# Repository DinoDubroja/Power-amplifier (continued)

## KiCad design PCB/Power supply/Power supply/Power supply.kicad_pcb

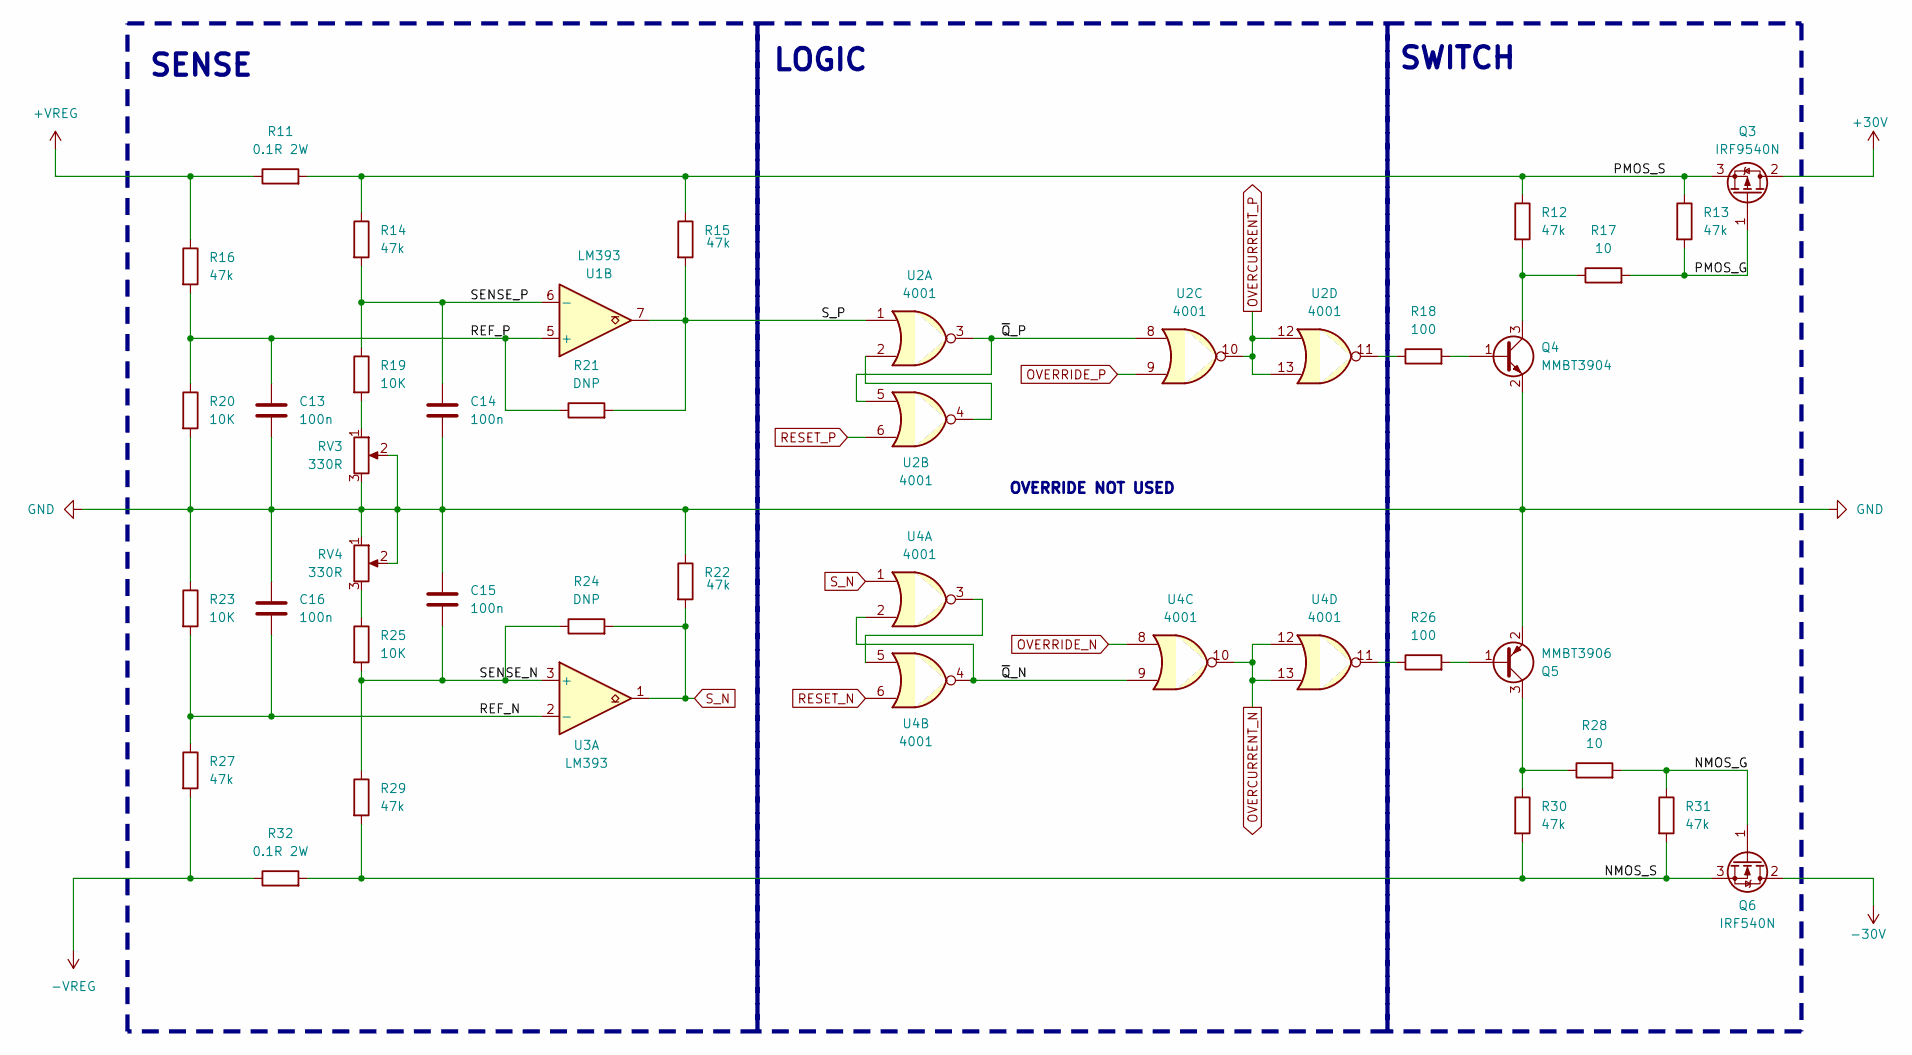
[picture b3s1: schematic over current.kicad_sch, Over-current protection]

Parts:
C13, C14, C15, C16: 100n; C_Rect_L7.0mm_W2.5mm_P5.00mm
Q3: IRF9540N; TO-220-3_Vertical
Q4: MMBT3904; SOT-23
Q5: MMBT3906; SOT-23
Q6: IRF540N; TO-220-3_Vertical
R11, R32: 0.1R 2W; R_Axial_DIN0309_L9.0mm_D3.2mm_P20.32mm_Horizontal
R12, R13, R14, R15, R16, R22, R27, R29, R30, R31: 47k; R_Axial_DIN0207_L6.3mm_D2.5mm_P10.16mm_Horizontal
R17, R28: 10; R_Axial_DIN0207_L6.3mm_D2.5mm_P10.16mm_Horizontal
R18, R26: 100; R_Axial_DIN0207_L6.3mm_D2.5mm_P10.16mm_Horizontal
R19, R20, R23, R25: 10K; R_Axial_DIN0207_L6.3mm_D2.5mm_P10.16mm_Horizontal
R21, R24: DNP; R_Axial_DIN0207_L6.3mm_D2.5mm_P10.16mm_Horizontal
RV3, RV4: 330R; Potentiometer_Bourns_3296W_Vertical
U1, U3: LM393; SOIC-8_3.9x4.9mm_P1.27mm
U2, U4: 4001; SOIC127P600X175-14N

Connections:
+30V: Q3.2 (D); also elsewhere on the board
+VREG: R11.1, R16.1; also elsewhere on the board
-30V: Q6.2 (D); also elsewhere on the board
-VREG: R27.2, R32.1; also elsewhere on the board
/Over-current/NMOS_G: Q6.1 (G), R28.2, R31.1
/Over-current/NMOS_S: Q6.3 (S), R29.2, R30.2, R31.2, R32.2
/Over-current/PMOS_G: Q3.1 (G), R13.2, R17.2
/Over-current/PMOS_S: Q3.3 (S), R11.2, R12.1, R13.1, R14.1, R15.1
/Over-current/REF_N: C16.2, R23.2, R27.1, U3.2 (-)
/Over-current/REF_P: C13.1, R16.2, R20.1, R21.1, U1.5 (+)
/Over-current/SENSE_N: C15.2, R24.1, R25.2, R29.1, U3.3 (+)
/Over-current/SENSE_P: C14.1, R14.2, R19.1, U1.6 (-)
/Over-current/S_P: R15.2, R21.2, U1.7, U2.1
/Over-current/~Q_N: U4.2, U4.4, U4.9
/Over-current/~Q_P: U2.3, U2.5, U2.8
GND: C13.2, C14.2, C15.1, C16.1, Q4.2 (E), Q5.2 (E), R20.2, R22.1, R23.1, RV3.2, RV3.3, RV4.1, RV4.2; also elsewhere on the board
unnamed: Q4.1 (B), R18.2
unnamed: Q4.3 (C), R12.2, R17.1
unnamed: Q5.1 (B), R26.2
unnamed: Q5.3 (C), R28.1, R30.1
unnamed: R18.1, U2.11
unnamed: R19.2, RV3.1
unnamed: R25.1, RV4.3
unnamed: R26.1, U4.11
unnamed: U2.2, U2.4
unnamed: U4.3, U4.5
OVERCURRENT_N: U4.10, U4.12, U4.13; also elsewhere on the board
OVERCURRENT_P: U2.10, U2.12, U2.13; also elsewhere on the board
OVERRIDE_N: U4.8; also elsewhere on the board
OVERRIDE_P: U2.9; also elsewhere on the board
RESET_N: U4.6; also elsewhere on the board
RESET_P: U2.6; also elsewhere on the board
S_N: R22.2, R24.2, U3.1, U4.1

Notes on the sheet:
SENSE
LOGIC
OVERRIDE NOT USED
SWITCH

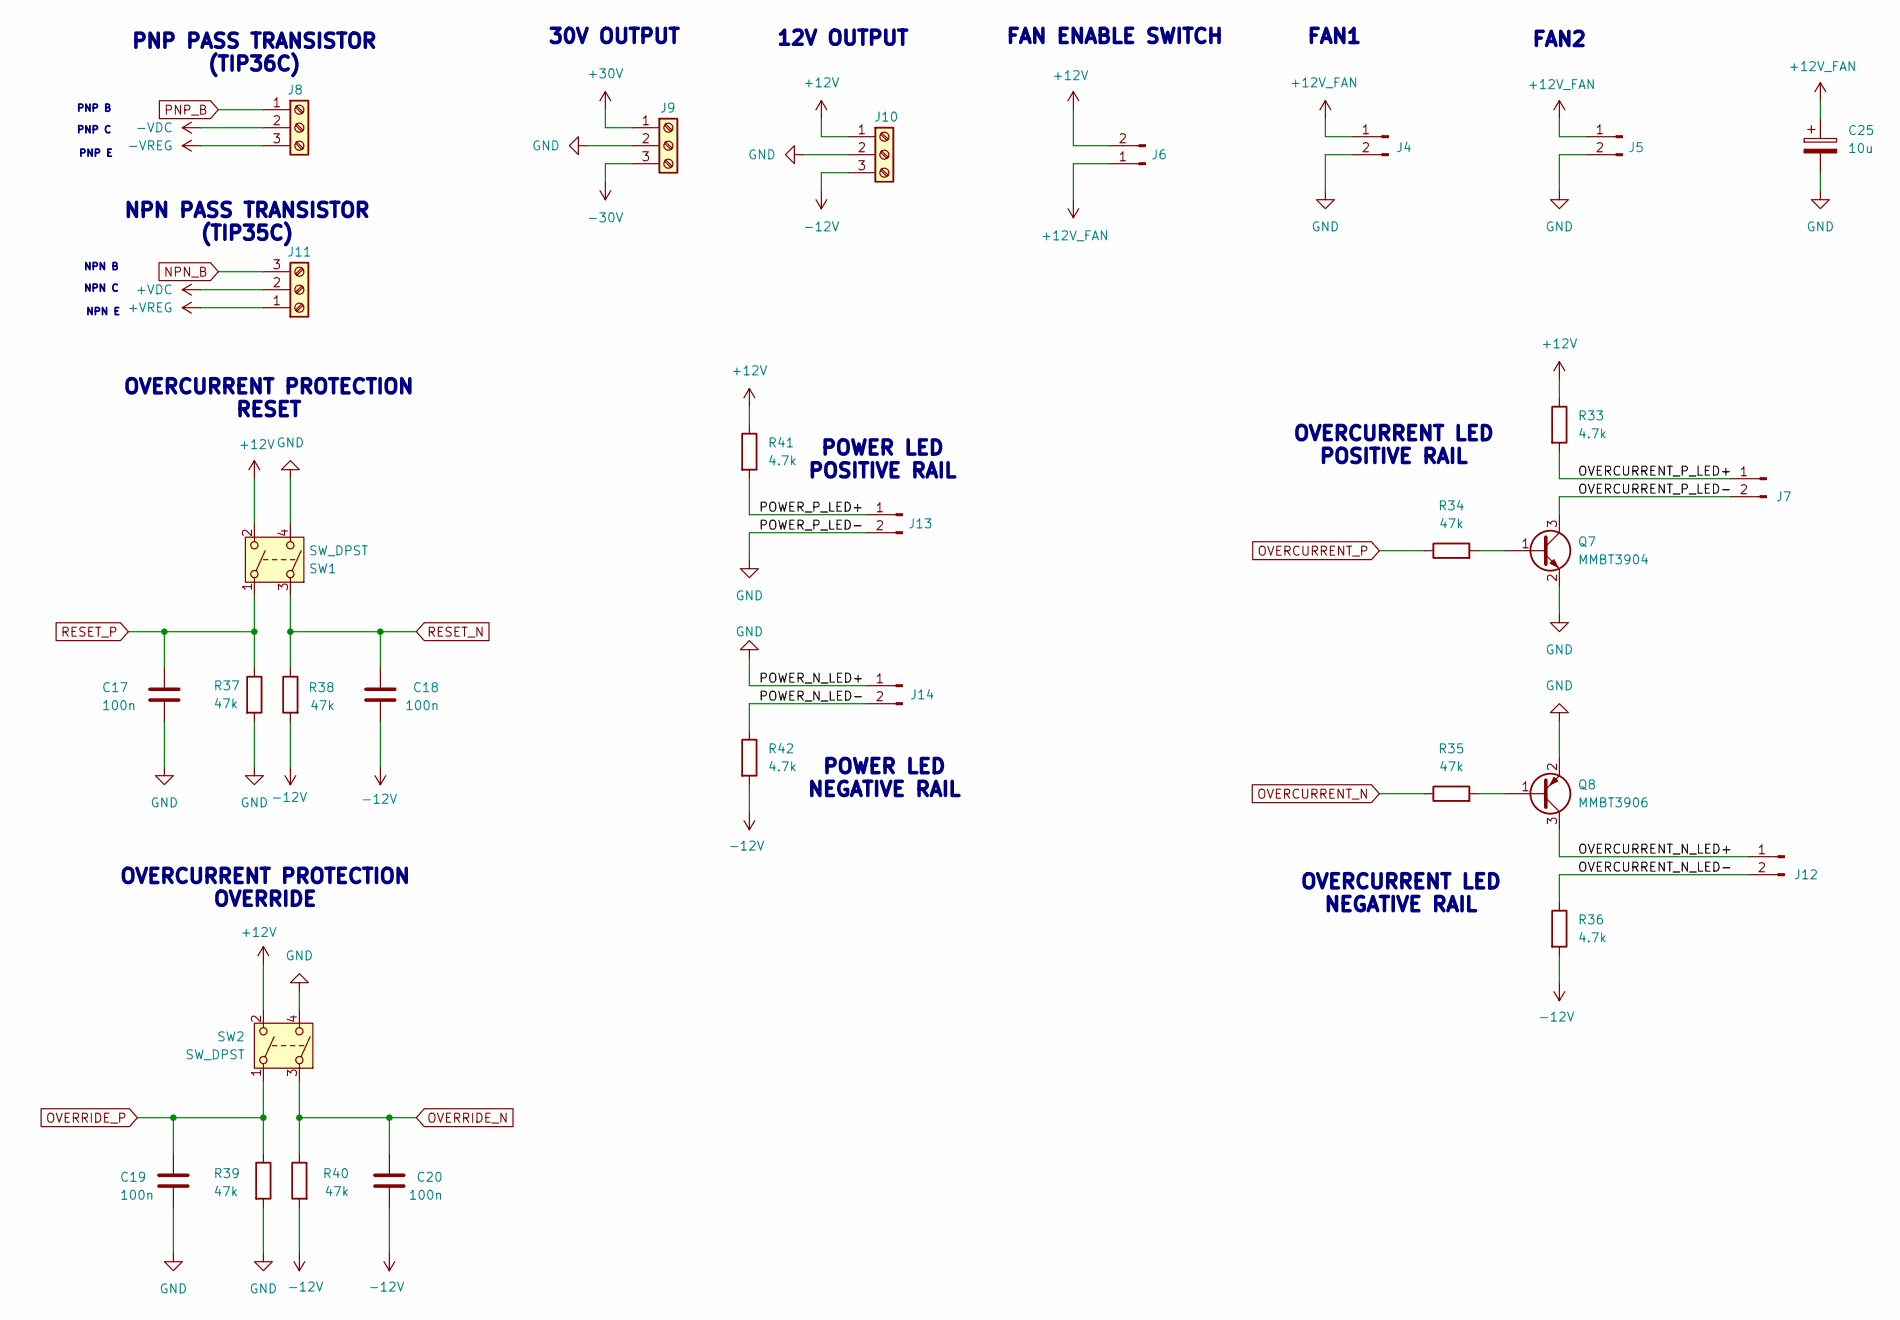
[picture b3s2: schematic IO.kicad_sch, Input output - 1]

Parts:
C17, C18, C19, C20: 100n; C_Rect_L7.0mm_W2.5mm_P5.00mm
C25: 10u; CP_Radial_D4.0mm_P2.00mm
J4, J5, J6, J7, J12, J13, J14: Conn_01x02_Pin; JST_XH_B2B-XH-A_1x02_P2.50mm_Vertical
J8, J9, J10, J11: Screw_Terminal_01x03; TerminalBlock_Phoenix_MKDS-1,5-3-5.08_1x03_P5.08mm_Horizont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
Q7: MMBT3904; SOT-23
Q8: MMBT3906; SOT-23
R33, R36, R41, R42: 4.7k; R_Axial_DIN0207_L6.3mm_D2.5mm_P10.16mm_Horizontal
R34, R35, R37, R38, R39, R40: 47k; R_Axial_DIN0207_L6.3mm_D2.5mm_P10.16mm_Horizontal
SW1, SW2: SW_DPST; JST_XH_B4B-XH-A_1x04_P2.50mm_Vertical

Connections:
+12V: J6.2, J10.1, R33.1, R41.1, SW1.2, SW2.2; also elsewhere on the board
+12V_FAN: C25.1, J4.1, J5.1, J6.1
+30V: J9.1; also elsewhere on the board
+VDC: J11.2; also elsewhere on the board
+VREG: J11.1; also elsewhere on the board
-12V: C18.2, C20.2, J10.3, R36.2, R38.2, R40.2, R42.2; also elsewhere on the board
-30V: J9.3; also elsewhere on the board
-VDC: J8.2; also elsewhere on the board
-VREG: J8.3; also elsewhere on the board
/IO/OVERCURRENT_N_LED+: J12.1, Q8.3 (C)
/IO/OVERCURRENT_N_LED-: J12.2, R36.1
/IO/OVERCURRENT_P_LED+: J7.1, R33.2
/IO/OVERCURRENT_P_LED-: J7.2, Q7.3 (C)
/IO/POWER_N_LED-: J14.2, R42.1
/IO/POWER_P_LED+: J13.1, R41.2
GND: C17.2, C19.2, C25.2, J4.2, J5.2, J9.2, J10.2, J13.2, J14.1, Q7.2 (E), Q8.2 (E), R37.2, R39.2, SW1.4, SW2.4; also elsewhere on the board
NPN_B: J11.3; also elsewhere on the board
unnamed: Q7.1 (B), R34.2
unnamed: Q8.1 (B), R35.2
OVERCURRENT_N: R35.1; also elsewhere on the board
OVERCURRENT_P: R34.1; also elsewhere on the board
OVERRIDE_N: C20.1, R40.1, SW2.3; also elsewhere on the board
OVERRIDE_P: C19.1, R39.1, SW2.1; also elsewhere on the board
PNP_B: J8.1; also elsewhere on the board
RESET_N: C18.1, R38.1, SW1.3; also elsewhere on the board
RESET_P: C17.1, R37.1, SW1.1; also elsewhere on the board

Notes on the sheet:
OVERCURRENT LED NEGATIVE RAIL
FAN2
NPN C
PNP PASS TRANSISTOR (TIP36C)
FAN ENABLE SWITCH
30V OUTPUT
PNP C
POWER LED NEGATIVE RAIL
OVERCURRENT PROTECTION RESET
POWER LED POSITIVE RAIL
12V OUTPUT
NPN PASS TRANSISTOR (TIP35C)
OVERCURRENT PROTECTION OVERRIDE
PNP E
PNP B
OVERCURRENT LED POSITIVE RAIL
FAN1
NPN E
NPN B

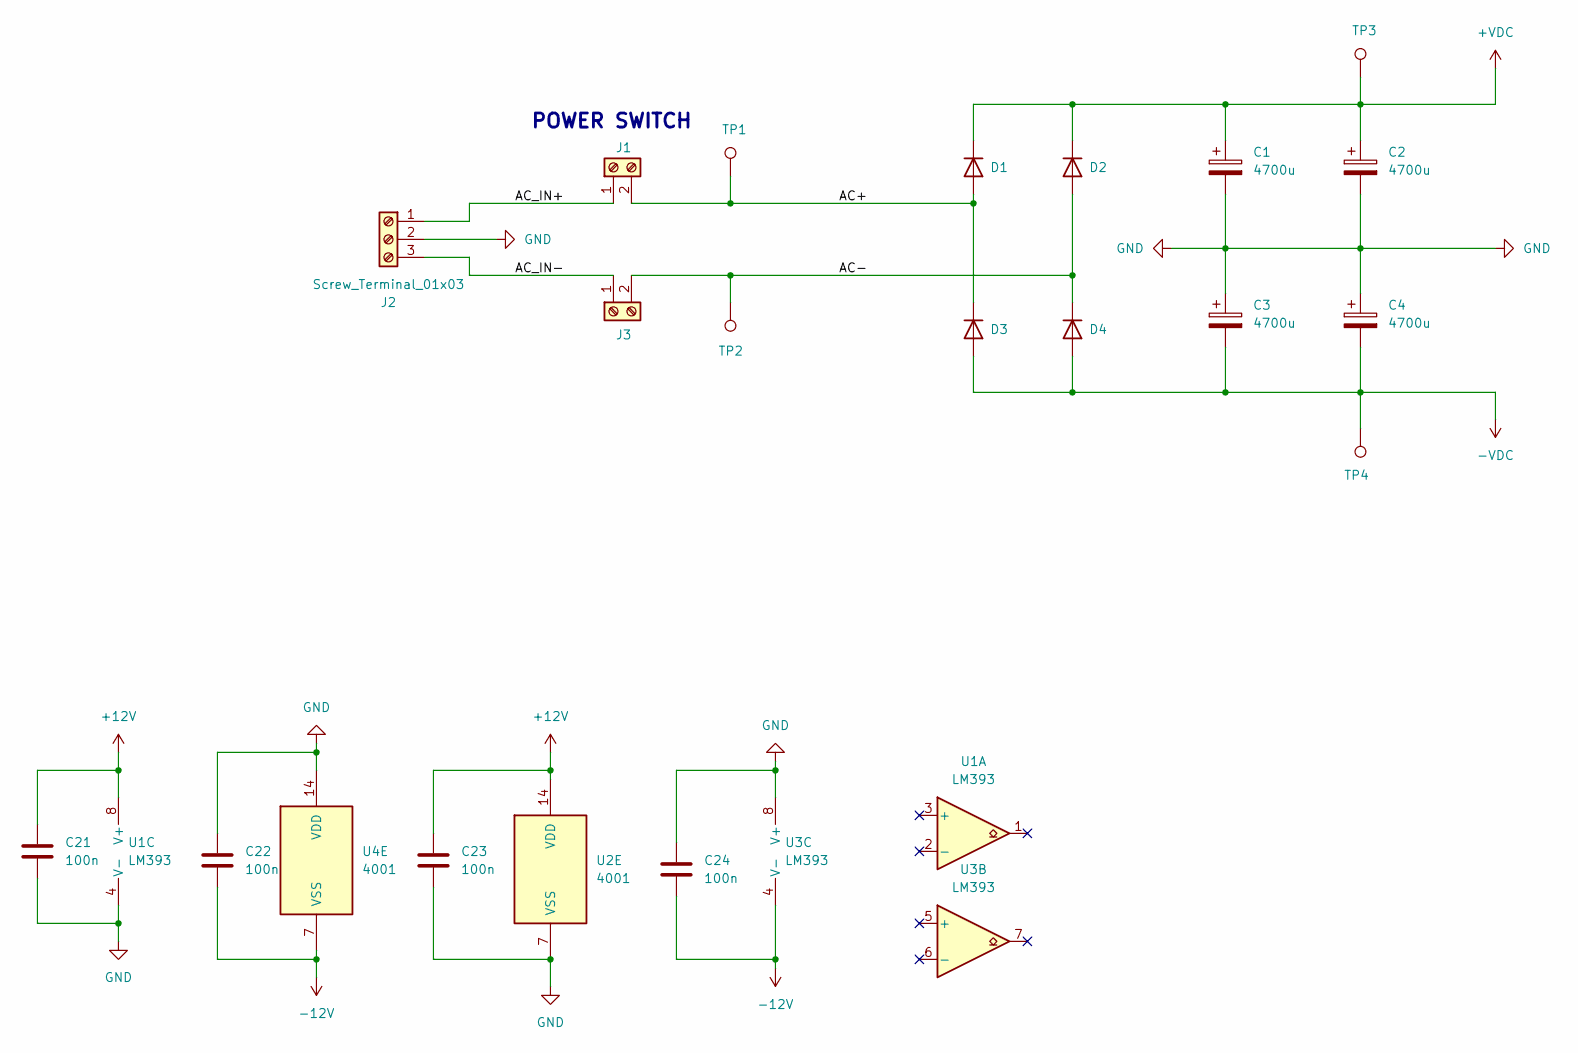
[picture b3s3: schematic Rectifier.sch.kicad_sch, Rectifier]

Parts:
C1, C2, C3, C4: 4700u; CP_Radial_D22.0mm_P10.00mm_SnapIn
C21, C22, C23, C24: 100n; C_Rect_L7.0mm_W2.5mm_P5.00mm
D1, D2, D3, D4: FERD20H100STS; TO254P483X1010X2035-3P; Mouser Part Number 511-FERD20H100STS
J1, J3: Screw_Terminal_01x02; TerminalBlock_Phoenix_MKDS-1,5-2-5.08_1x02_P5.08mm_Horizont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
J2: Screw_Terminal_01x03; TerminalBlock_Phoenix_MKDS-1,5-3-5.08_1x03_P5.08mm_Horizont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
TP1, TP2, TP3, TP4: Pin_D1.3mm_L10.0mm_W3.5mm_Flat
U1, U3: LM393; SOIC-8_3.9x4.9mm_P1.27mm
U2, U4: 4001; SOIC127P600X175-14N

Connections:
+12V: C21.1, C23.1, U1.8 (V+), U2.14 (VDD); also elsewhere on the board
+VDC: C1.1, C2.1, D1.2 (K), D2.2 (K), TP3.1; also elsewhere on the board
-12V: C22.2, C24.2, U3.4 (V-), U4.7 (VSS); also elsewhere on the board
-VDC: C3.2, C4.2, D3.1 (A), D3.3 (A), D4.1 (A), D4.3 (A), TP4.1; also elsewhere on the board
/Rectifier/AC+: D1.1 (A), D1.3 (A), D3.2 (K), J1.2, TP1.1
/Rectifier/AC-: D2.1 (A), D2.3 (A), D4.2 (K), J3.2, TP2.1
/Rectifier/AC_IN+: J1.1, J2.1
/Rectifier/AC_IN-: J2.3, J3.1
GND: C1.2, C2.2, C3.1, C4.1, C21.2, C22.1, C23.2, C24.1, J2.2, U1.4 (V-), U2.7 (VSS), U3.8 (V+), U4.14 (VDD); also elsewhere on the board

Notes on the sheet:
POWER SWITCH

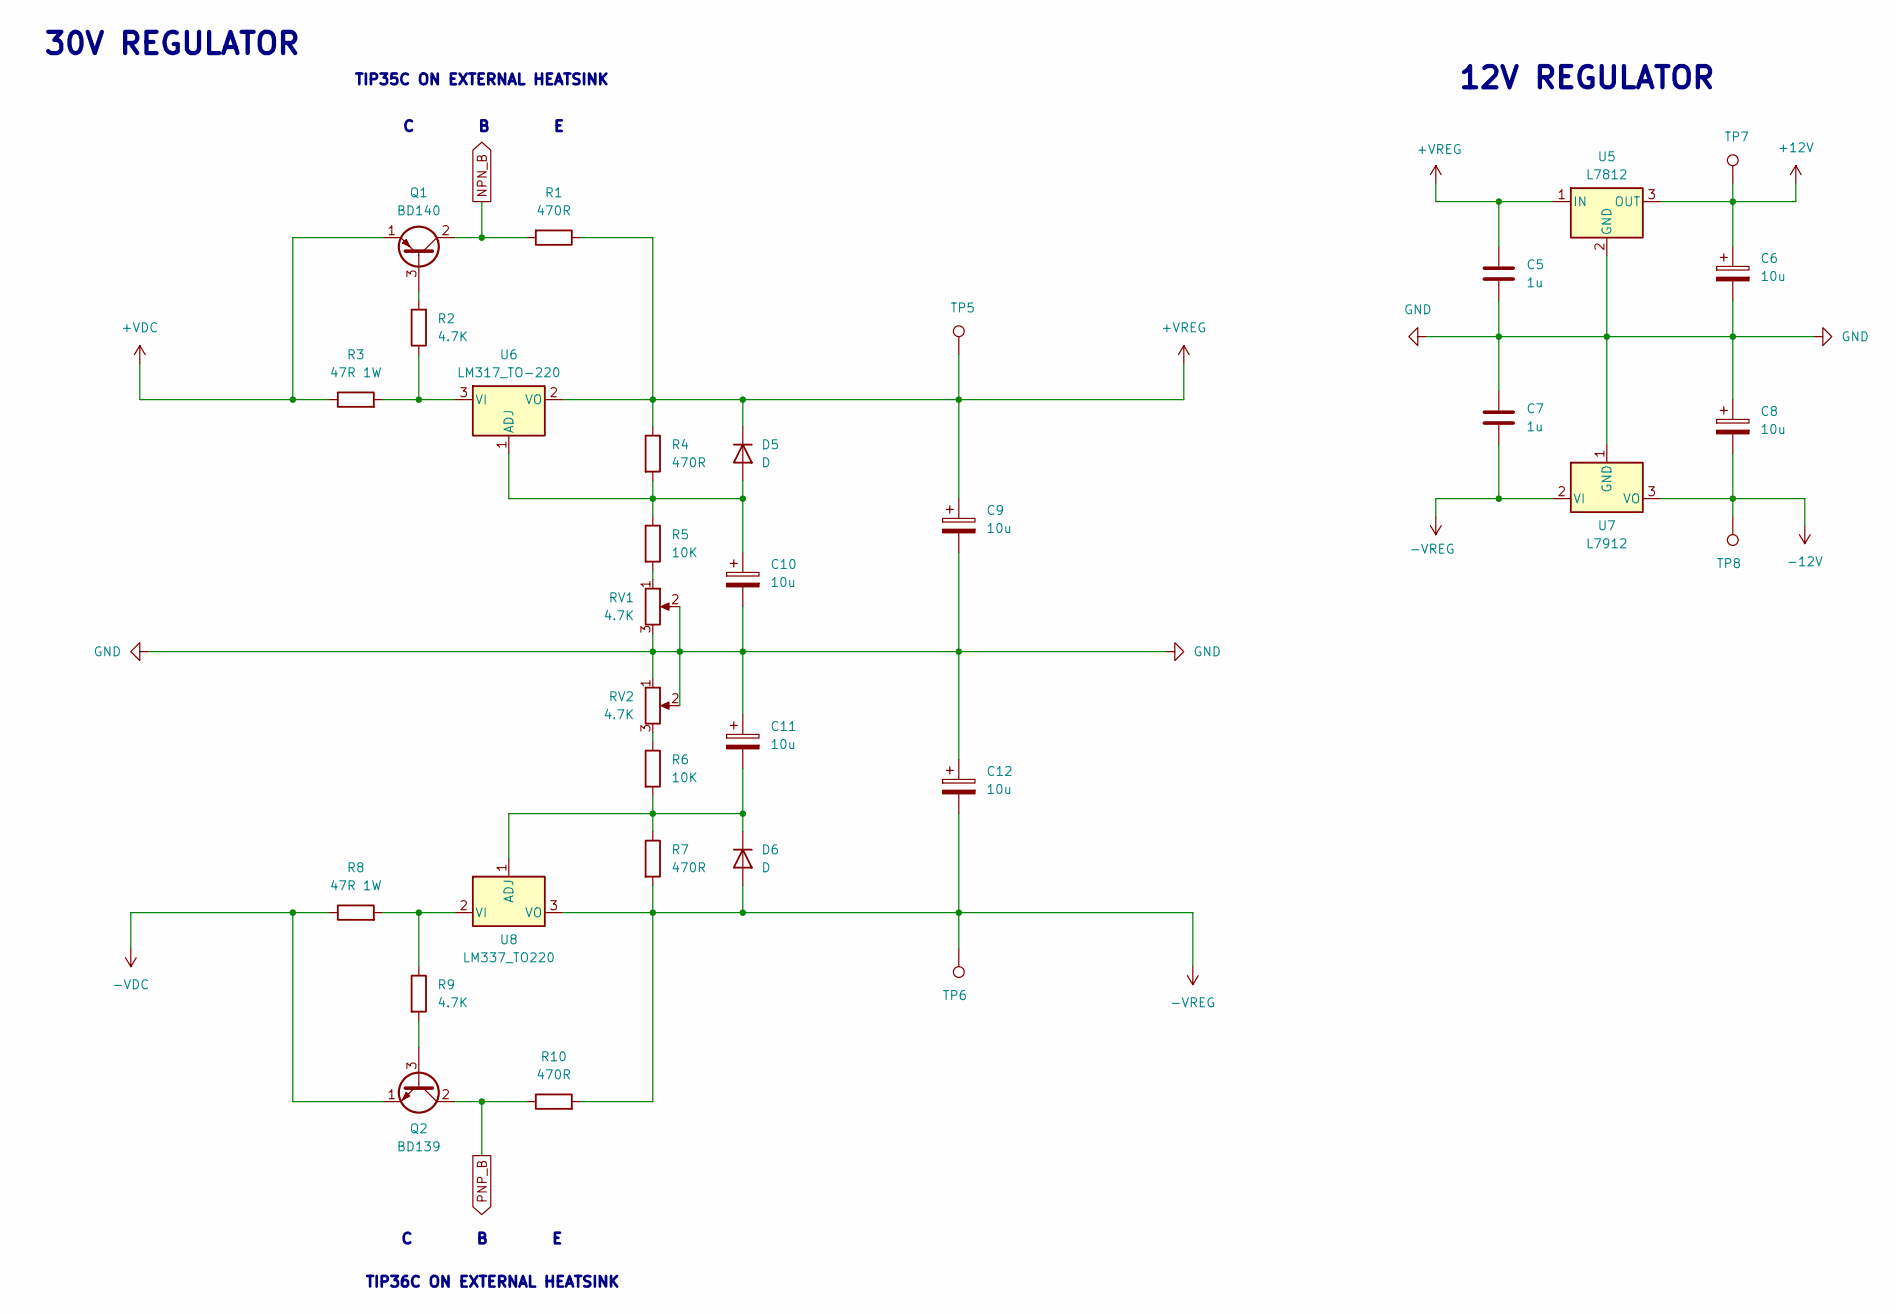
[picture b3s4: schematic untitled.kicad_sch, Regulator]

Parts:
C5, C7: 1u; C_Rect_L7.0mm_W6.0mm_P5.00mm
C6, C8, C9, C10, C11, C12: 10u; CP_Radial_D4.0mm_P2.00mm
D5, D6: D; D_A-405_P10.16mm_Horizontal
Q1: BD140; TO-126-3_Vertical
Q2: BD139; TO-126-3_Vertical
R1, R4, R7, R10: 470R; R_Axial_DIN0207_L6.3mm_D2.5mm_P10.16mm_Horizontal
R2, R9: 4.7K; R_Axial_DIN0207_L6.3mm_D2.5mm_P10.16mm_Horizontal
R3, R8: 47R 1W; R_Axial_DIN0207_L6.3mm_D2.5mm_P15.24mm_Horizontal
R5, R6: 10K; R_Axial_DIN0207_L6.3mm_D2.5mm_P10.16mm_Horizontal
RV1, RV2: 4.7K; Potentiometer_Bourns_3296W_Vertical
TP5, TP6, TP7, TP8: Pin_D1.3mm_L10.0mm_W3.5mm_Flat
U5: L7812; TO-220-3_Vertical
U6: LM317_TO-220; TO-220-3_Vertical
U7: L7912; TO-220-3_Vertical
U8: LM337_TO220; TO-220-3_Vertical

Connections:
+12V: C6.1, TP7.1, U5.3 (OUT); also elsewhere on the board
+VDC: Q1.1 (E), R3.1; also elsewhere on the board
+VREG: C5.1, C9.1, D5.1 (K), R1.1, R4.1, TP5.1, U5.1 (IN), U6.2 (VO); also elsewhere on the board
-12V: C8.2, TP8.1, U7.3 (VO); also elsewhere on the board
-VDC: Q2.1 (E), R8.1; also elsewhere on the board
-VREG: C7.2, C12.2, D6.2 (A), R7.2, R10.2, TP6.1, U7.2 (VI), U8.3 (VO); also elsewhere on the board
GND: C5.2, C6.2, C7.1, C8.1, C9.2, C10.2, C11.1, C12.1, RV1.2, RV1.3, RV2.1, RV2.2, U5.2 (GND), U7.1 (GND); also elsewhere on the board
NPN_B: Q1.2 (C), R1.2; also elsewhere on the board
unnamed: C10.1, D5.2 (A), R4.2, R5.1, U6.1 (ADJ)
unnamed: C11.2, D6.1 (K), R6.2, R7.1, U8.1 (ADJ)
unnamed: Q1.3 (B), R2.2
unnamed: Q2.3 (B), R9.2
unnamed: R5.2, RV1.1
unnamed: R6.1, RV2.3
unnamed: R2.1, R3.2, U6.3 (VI)
unnamed: R8.2, R9.1, U8.2 (VI)
PNP_B: Q2.2 (C), R10.1; also elsewhere on the board

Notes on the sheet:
C B E
TIP36C ON EXTERNAL HEATSINK
TIP35C ON EXTERNAL HEATSINK
30V REGULATOR
12V REGULATOR

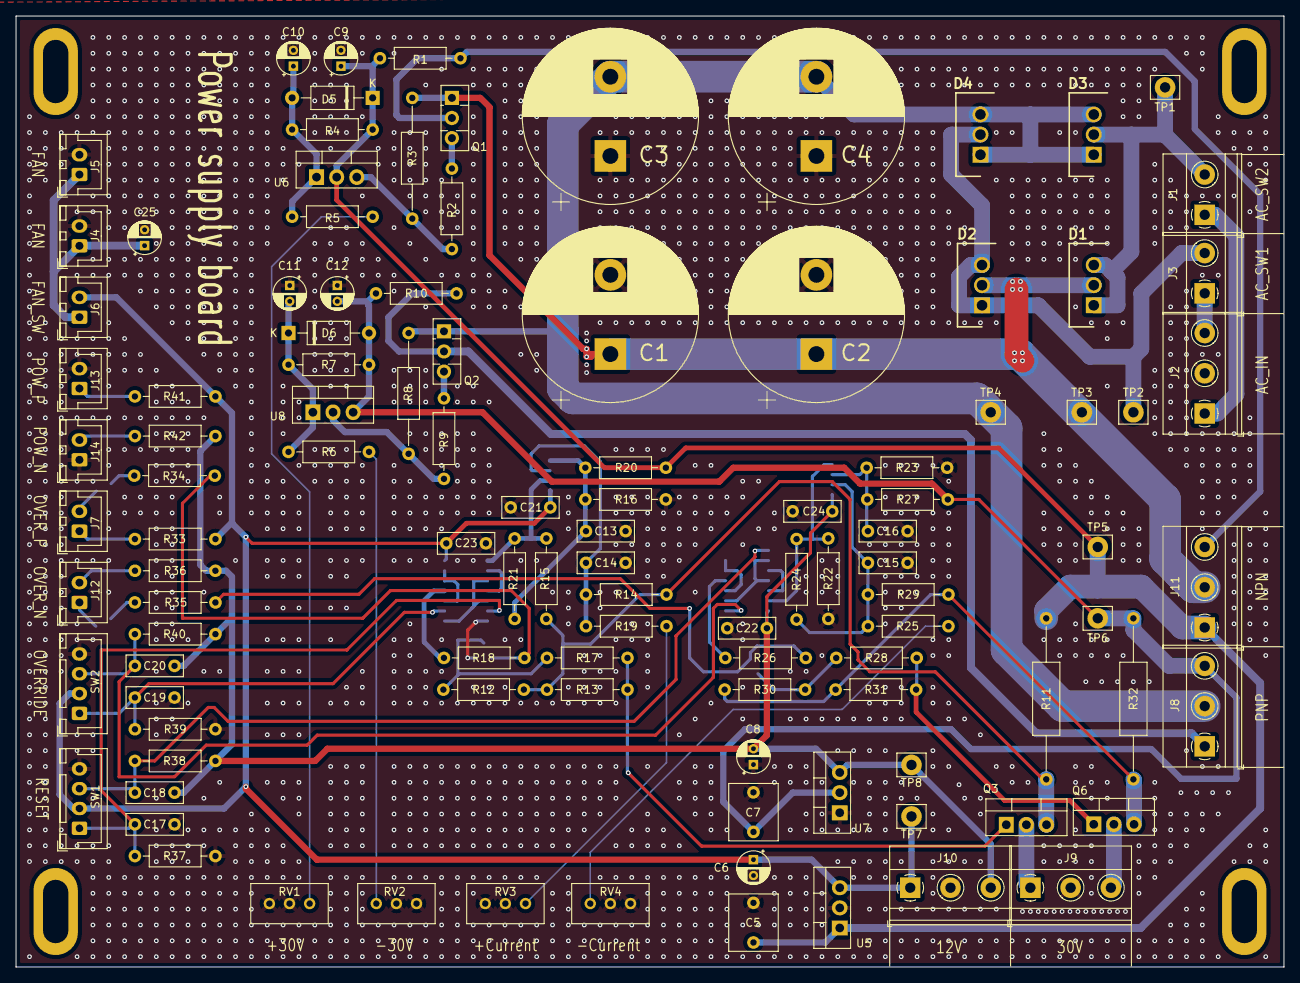
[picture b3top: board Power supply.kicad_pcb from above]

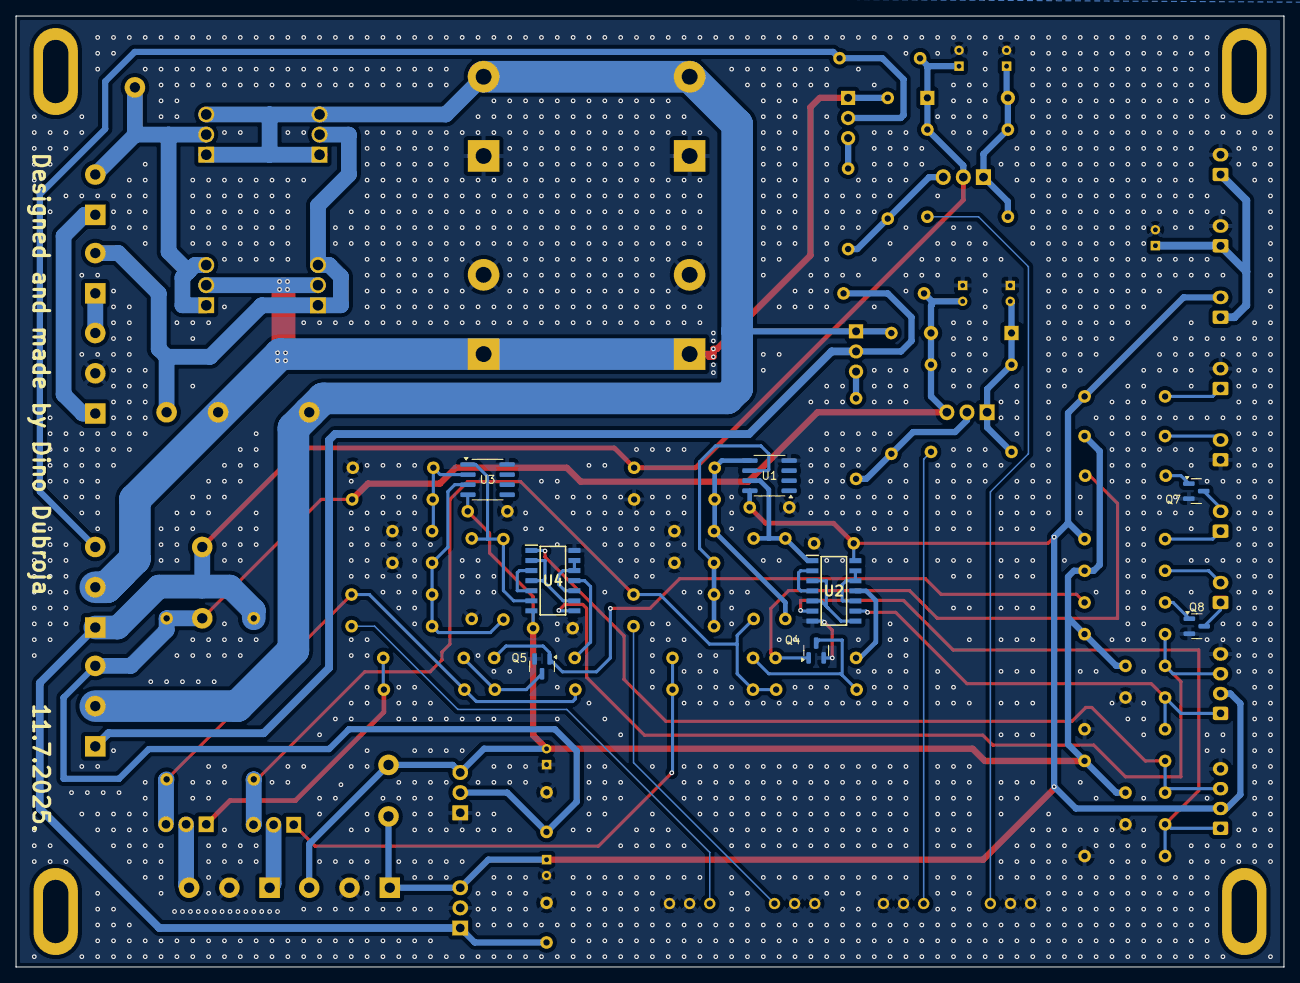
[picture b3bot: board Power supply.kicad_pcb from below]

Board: 2 copper layers, 160.0 x 120.0 mm, 117 parts (8 on the bottom side), 60 nets.

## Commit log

2025-07-14 Added and modified .gitignore
2025-07-14 Project files uploaded (start)
2025-07-14 Minor changes to PCB design
2025-07-22 Worked on simulations (ouput stage)
2025-07-29 Added new simulations and datasheets
2025-07-30 Added datasheets and step files. Added "Amplifier BODE" folder
2025-08-08 Made Power Supply schematic prettier
2025-08-28 Did some simulations, fixed some mistakes in PSU schematic
2025-08-28 Added and worked on "Amplifier" KiCAD project
2025-08-29 Worked on "amplifier" schematic
2025-08-29 Worked on amplifier schematic
2025-10-12 Big commit after a long time :)
